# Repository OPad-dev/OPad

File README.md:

# OPad

**Low-Latency ESP32-S3 Rhythm Gaming Keypad & Telemetry Display**

A deterministic, ultra-low-latency mechanical keypad and live telemetry HUD designed for competitive osu!, osu!lazer, and rhythm games on **Linux and Windows 10/11**.

---

## ⚡ Core Principle: Latency Always Wins

> **"If a feature measurably worsens keyboard latency or latency jitter, the feature is reduced, deferred, frozen during gameplay, or removed."**

The keypad functions as a standalone 1000 Hz USB HID keyboard out of the box with zero host software running. Auxiliary features (LVGL telemetry, SQLite persistence, system tray, and tosu integration) are completely isolated from the keypress critical path.

---

## 🏗️ System Architecture

```text
                      +-------------------+
                      |    osu!lazer      |
                      +---------+---------+
                                | (observes)
                                v
                      +-------------------+
                      |       tosu        |
                      +---------+---------+
                                | (WebSocket v2)
                                v
+--------------------+   +-------------------------+
|      opad-gui      |   |       opad-daemon       |
|     (Rust/iced)    |<->|         (Rust)          |
|  - System Tray     |IPC|  - State Machine        |
|  - Layout Designer |   |  - SQLite Storage       |
|  - Configuration   |   |  - Headless Service     |
|  - Diagnostics     |   |  - tosu & Device Owner  |
+--------------------+   +------------+------------+
                                      |
                           USB CDC    |    USB HID (1000 Hz)
                                      |
                                      v
                         +-------------------------+
                         |  ESP32-S3 Touch LCD 2   |
                         |  - Eager Debounce ISR   |
                         |  - Core 0: Input & HID  |
                         |  - Core 1: LVGL & CDC   |
                         |  - ST7789 Telemetry HUD |
                         +-------------------------+
```

---

## 🔌 Hardware Target & Switch Wiring

### Supported Hardware
- **Board**: **Waveshare ESP32-S3-Touch-LCD-2** (ESP32-S3, 16MB Flash, 8MB PSRAM, 2.0" ST7789 LCD)
- **Switches**: Any two standard MX-compatible mechanical switches.

### Switch Pinout (Header P2)
Standard MX mechanical switches have no polarity. Connect each switch between its designated GPIO and ground:

| Input | Board Header & Pin | GPIO | Switch Connection |
|---|---|---|---|
| **Key 1** (Default `Z`) | **Header P2, Pin 11** | `GPIO 14` | Pin A -> Pin 11, Pin B -> GND (Pin 13) |
| **Key 2** (Default `X`) | **Header P2, Pin 12** | `GPIO 9` | Pin A -> Pin 12, Pin B -> GND (Pin 2) |
| **Ground** | **Header P2, Pin 13 / Pin 2** | `GND` | Ground Reference |

*Note: Pins 11, 12, and 13 are directly adjacent on Header P2 for simple breadboard/Dupont jumper wiring.*

These are the defaults. Each key's pin can be changed in the app under **Settings → Keys**. The list only offers header pins that work with a switch to GND:

| Header | Pins (GPIO) |
|---|---|
| **P1** | 1 (`GPIO 2`), 2 (`GPIO 4`), 3 (`GPIO 6`), 4 (`GPIO 16`), 6 (`GPIO 18`), 7 (`GPIO 21`), 8 (`GPIO 8`), 9 (`GPIO 7`), 10 (`GPIO 10`) |
| **P2** | 7 (`GPIO 15`), 8 (`GPIO 13`), 9 (`GPIO 11`), 10 (`GPIO 12`), 11 (`GPIO 14`), 12 (`GPIO 9`) |

Left out: `GPIO 19/20` (USB), `GPIO 43/44` (UART0 console), `GPIO 47/48` (touch and IMU I2C) and `GPIO 17` (pulled down on the board). Most listed pins are also wired to the camera connector, so don't use them with a camera fitted.

---

## 🛠️ Building From Source

### 1. Prerequisites (Ubuntu / Debian)
```bash
sudo apt update
sudo apt install -y build-essential pkg-config libasound2-dev libudev-dev \
    libx11-dev libxkbcommon-dev libwayland-dev libfontconfig1-dev libdbus-1-dev
```

### 2. Desktop Software Suite (Rust)
```bash
cd desktop
cargo build --release
```
The compiled binaries are produced in `desktop/target/release/`:
- `opad-daemon`: Background service.
- `opad-gui`: Graphical configuration, layout designer, and system tray.
- `opadctl`: Command-line management tool.

### 3. Firmware Build (ESP-IDF v5.5.2)
```bash
cd firmware
idf.py set-target esp32s3
idf.py build
```

---

## ⚡ Flashing the Firmware

### Option A: Via `opadctl` (Recommended)
`opadctl` drives `espflash` directly and needs no shell script and no ESP-IDF
toolchain. It asks the daemon to release the serial port first, reboots the pad
into the ROM download bootloader hands-free, writes the image and reboots back
into the app — on Linux and on Windows, with the app running:

```bash
# Update the app image only (ota_0 at 0x20000)
opadctl flash firmware/build/opad-firmware.bin

# Recovery flash: bootloader + partition table + OTA data + app
opadctl flash --full firmware/build
```

It also works with no daemon running at all, which is the state a recovery
flash usually happens in.

### Option B: Via ESP-IDF
```bash
cd firmware
idf.py -p /dev/ttyACM0 flash
```

If the pad will not enter download mode or has to be returned to stock, see
[Recovery, Reflashing & Unbinding](docs/recovery.md).

---

## 🪟 Windows Setup & Installation

**The pad needs none of this to work as a keyboard.** Plug it into any Windows
10 or 11 machine and it types immediately: HID binds to the inbox
`hidclass.sys` and the CDC port to the inbox `usbser.sys`. No `.inf`, no
WinUSB, no Zadig, no install. The software below is for configuring it, the
telemetry HUD and the lifetime counters.

1. Download `opad-setup-<version>.exe` from the GitHub Releases page and run it.
2. It installs the daemon, the GUI and `opadctl`, bundles tosu, and configures
   both to start at login. There is nothing else to do.

> **SmartScreen will warn you.** The installer is **not code-signed** yet:
> OPad is applying to SignPath Foundation for free OSS signing, which
> requires the repository to be public first. Until then, Windows shows
> "Windows protected your PC" — choose **More info → Run anyway**. Check the
> download against `SHA256SUMS` on the release page if you would rather verify
> it than trust the dialog.

Uninstall from Settings → Apps. It removes everything it installed, including
the two `Run` registry values, and asks before it touches your `opad.db` —
so a reinstall keeps your lifetime counters unless you say otherwise.

**To reset a pad completely, or hand it to someone else**, see
[Recovery, Reflashing & Unbinding](docs/recovery.md). There is no unpair button
in the app, deliberately: the only unbind is a documented reflash, and it erases
the pad's lifetime counters along with the owner record.

---

## 🚀 Linux Setup & Installation

### Option A: Pre-built Packages (Recommended)

Pre-built packages are on the GitHub Releases page. The `.deb` and `.rpm` set
up everything: the udev rule, the daemon's systemd user service, tray autostart,
the bundled `espflash`, and the ptrace capability tosu needs to read osu!'s
memory (see [docs/troubleshooting.md](docs/troubleshooting.md) §2).

Supported: every Ubuntu LTS and Debian release in support (Ubuntu 22.04, 24.04,
26.04; Debian 12, 13), RHEL / AlmaLinux / Rocky 9 and 10, current Fedora and
Arch. The release packages, bundled tosu included, need glibc 2.28 or newer.

#### Debian / Ubuntu / Pop!_OS (`.deb`):
```bash
sudo apt install ./opad_<version>_amd64.deb
# Or via dpkg:
sudo dpkg -i opad_<version>_amd64.deb
```

#### Fedora / RHEL / openSUSE (`.rpm`):
```bash
sudo dnf install ./opad-<version>.x86_64.rpm
```

#### Standalone AppImage:
```bash
chmod +x opad-x86_64.AppImage
./opad-x86_64.AppImage
```
The AppImage installs nothing system-wide. On first run it offers to install
the udev rule (it asks for your password), or run
`./opad-x86_64.AppImage install-udev` yourself. It cannot give tosu the ptrace
capability; `opadctl setup` and the Diagnostics page explain the alternative.

#### Arch Linux:
The repository's `PKGBUILD` builds from source (tosu runs on the system
`nodejs`, so see troubleshooting §2 about ptrace):
```bash
makepkg -si
```

---

### Option B: Installing From Source

#### 1. System-wide Install:
```bash
make
sudo make install
```

#### 2. User-local Install (`~/.local`):
```bash
make
make install-user
systemctl --user daemon-reload
systemctl --user enable --now opad-daemon.service
```

#### 3. Manual Udev Rules:
If not installing from package, allow non-root user access to USB CDC and ROM bootloader devices:
```bash
sudo cp packaging/linux/udev/70-opad.rules /etc/udev/rules.d/
sudo udevadm control --reload-rules && sudo udevadm trigger
```

---

## 💻 CLI Quick Reference (`opadctl`)

```bash
# Check device, daemon, and tosu state
opadctl status

# Trigger safe reconciliation
opadctl sync

# Export portable JSON backup
opadctl export backup.json

# Import validated backup
opadctl import backup.json

# Flash firmware image directly over USB
opadctl flash firmware/build/opad-firmware.bin

# Recovery flash (bootloader, partition table, OTA data and app)
opadctl flash --full firmware/build

# Reboot the pad into the ROM download bootloader and leave it there
opadctl bootloader

# Stream real-time diagnostic logs
opadctl monitor
```

---

## 📄 Documentation
- [Documentation Hub & Wiki](docs/README.md)
- [System Architecture](docs/architecture.md)
- [Project Roadmap & Hardware Variants](docs/roadmap.md)
- [OPad on Windows — as built](docs/windows-portability.md)
- [USB Framing & Protocol](docs/protocol.md)
- [Counter Reconciliation, Recovery & Unbinding](docs/recovery.md) — including the reflash / unbind path
- [Latency Testing Methodology](docs/latency-testing.md)
- [Testing & Hardware Checklist](docs/testing-checklist.md)
- [Technical Specification v1](docs/specs/technical-spec-v1.md)
- [Rapid Trigger v2 Specification](docs/specs/v2-rapid-trigger.md)

---

## 📦 Third-Party Software

OPad bundles or interacts with the following third-party software:

### tosu
- **Project**: [tosu](https://github.com/KotRikD/tosu)
- **Author**: Mikhail Babynichev and the tosu contributors
- **License**: [GNU Lesser General Public License v3.0 (LGPL-3.0)](licenses/tosu/LICENSE)
- **Redistribution Notice**: See [licenses/tosu/NOTICE](licenses/tosu/NOTICE)
- **User Replacement Rights**: Under the terms of LGPL-3.0, users are entitled to replace the bundled tosu binary with their own version. You can point the `OPAD_TOSU_PATH` (or legacy `OSUPAD_TOSU_PATH`) environment variable to a custom tosu executable, or configure an external path in the OPad desktop GUI (**Settings → tosu**).

---

## ⚖️ Trademark Disclaimer
OPad is an independent open-source hardware and software project. OPad is not affiliated with, endorsed by, or sponsored by ppy Pty Ltd or osu!. "osu!" is a registered trademark of ppy Pty Ltd.

---

## 📜 License
OPad is free and open source, software and hardware:

- **Software** — the firmware, the desktop app (daemon, GUI, CLI), the protocol, the scripts and the documentation — is licensed under the [GNU General Public License v3.0 or later](LICENSE) (`GPL-3.0-or-later`).
- **Hardware** — everything in [`hardware/`](hardware/): the PCB designs, footprints and symbols, the enclosure CAD and the production files — is licensed under the [CERN Open Hardware Licence v2, Strongly Reciprocal](hardware/LICENSE) (`CERN-OHL-S-2.0`). The scripts in `hardware/` that generate and check those files are software, under `GPL-3.0-or-later`.

You may build, modify and sell OPad. If you distribute a modified version, of the software or of the hardware, you must publish its source under the same licence. Every file's licence is recorded in [`REUSE.toml`](REUSE.toml).

Third-party components keep their own open licenses and ship with their notices:
- [tosu](licenses/tosu/LICENSE) (LGPL-3.0), built from upstream source and bundled with the desktop packages, see the section above. Not stored in this repository.
- [Montserrat](desktop/gui/assets/fonts/Montserrat-OFL.txt) fonts embedded in the GUI (SIL Open Font License 1.1).
- [nanopb](firmware/main/protocol/nanopb/LICENSE.txt) protobuf runtime vendored in the firmware (zlib license).

Libraries pulled in at build time (Rust crates, ESP-IDF components such as LVGL and TinyUSB) are not stored here and are used under their own permissive licenses.

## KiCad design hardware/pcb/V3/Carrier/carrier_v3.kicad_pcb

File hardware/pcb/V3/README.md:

# OPad V3 PCBs

| Board | Folder | Size | Status |
|---|---|---|---|
| Controller carrier V3 | `Carrier/` | 35.0 × 48.2 mm (the V1 outline plus a lug in the window for the USB cable) | Designed, routed, checked. **Not ordered, not built** |
| USB board V3 | `USB/` | 20.0 × 22.0 mm | Designed, routed, checked (2026-10-28). **Not ordered, not built** |
| MX input module V3 | `MX/` | 71.05 × 24.0 mm, 3 keys | Designed, routed, checked. **Not ordered, not built** |
| HE input module V3 | `HE/` | 71.05 × 24.0 mm, 3 keys | Designed, routed, checked. **Not ordered, not built** |

These replace every V1/V2 board (decisions H10–H18 and section 4.2 in
`docs/specs/hardware-redesign-brief.md`). **No firmware supports them yet.**
The work still to do is listed under "Before ordering" below.

## What is different from V1

- **Module cable:** a 14-way, 1.0 mm FFC replaces the JST SH 8-pin. It is reversible
  (a reversed cable only swaps signals between ESP32 pins, see Cables).
- **USB-C on its own board** at the case's rear wall (H18). It has ESD protection, a VBUS
  ferrite and capacitors, and a Schottky so a cable in the Waveshare's own port cannot
  feed this one. An 8-way FFC that reads the same from either end takes 5 V, D+ and D−
  to the carrier, which passes them to P1-14, P1-11 (GPIO20) and P1-12 (GPIO19).
  The case seats it on pins in its two M2 holes and clamps it from above; stops and the
  rear wall take the plug's push and pull, so the header sockets never do. The path is passive, so flashing and recovery work over it as over
  the Waveshare's own port.
- **The carrier's USB connector** sits on a lug in the window's USB-end rear corner,
  mouth on the USB-end edge: P1's sockets fill the rear edge, and the lug keeps clear of
  the M2 hole at the USB-end rear corner. (The V3 case does not use that hole: the USB
  board lies under it, so a support presses the rear rail instead.)
- **Three keys** on both modules, and **four corner holes** for the case's locating pins.
- **HE:**
  - The ADC is an **ADS7028** (C880341), the ADS7038's sibling. It has the same pins,
    registers, averaging and CRC, and it is in JLCPCB's assembly stock. The ADS7038 is
    only on LCSC.
  - An **LP5907 LDO** powers the sensors and the ADC reference from the cable's 5 V,
    not from the Waveshare's buck-converter 3V3.
  - CS has a pull-up, and the SPI lines have ESD protection.
- **Every part is on one side:** the top of the carrier and the USB board, the bottom of
  the modules.

## Cables

### Module (14-way FFC, 1.0 mm, any type A or B, 80 mm in the V3 case)

| Contact | 1 | 2 | 3 | 4 | 5 | 6 | 7 | 8 | 9 | 10 | 11 | 12 | 13 | 14 |
|---|---|---|---|---|---|---|---|---|---|---|---|---|---|---|
| Carrier | GND | 5V | 3V3 | GPIO8 | GPIO6 | GND | GPIO2 | GPIO4 | GND | GPIO10 | GPIO7 | 3V3 | 5V | GND |
| HE | GND | 5V | 3V3 | ID | MISO | GND | SCLK | MOSI | GND | CS | – | 3V3 | 5V | GND |
| MX | GND | – | 3V3 | ID | KEY3 | GND | – | – | GND | KEY1 | KEY2 | 3V3 | – | GND |

A reversed cable connects contact k to 15 − k. Power and ground still meet power and
ground. The module's ID arrives on GPIO7 instead of GPIO8 (both are ADC1 pins), and the
firmware swaps the other pins in the GPIO matrix. `hardware/verify/tests/test_system.py`
follows every pin both ways round. MX keeps KEY1 = GPIO10 and KEY2 = GPIO7, as on V1.

Module IDs: MX V3 = 47k/100k = 2.24 V, HE V3 = 100k/100k = 1.65 V (the class HE V2
reserved, since the ADC and pins are the same). Firmware cut-offs: 0.68 / 1.35 / 1.95 / 2.6 V.

### USB (8-way FFC, 1.0 mm, any type A or B, 80 mm in the V3 case)

| Contact | 1 | 2 | 3 | 4 | 5 | 6 | 7 | 8 |
|---|---|---|---|---|---|---|---|---|
| USB board and carrier | GND | 5V | D− | D+ | D+ | D− | 5V | GND |

The pinout reads the same from either end, so a reversed cable (k to 9 − k) meets the
same nets. D+ and D− each use two conductors, joined on both boards. The two 5V contacts
carry 1 A together (0.5 A each, connector datasheet). The connectors are a different width
from the module's, so the two cables cannot be swapped. `test_system.py` follows the jack's
D+, D− and 5 V to GPIO20, GPIO19 and P1-14 with the cable both ways round.

## Checks (MX 2026-10-23; carrier, USB, HE 2026-10-29)

| Check | Carrier | USB | MX | HE |
|---|---|---|---|---|
| KiCad ERC, DRC with zones refilled, schematic parity | 0 | 0 | 0 | 0 |
| `hardware/verify` (fab files against the intended netlist, datasheet pin drawings, JLCPCB's own part models at the CPL) | 0 errors | 0 errors | 0 errors | 0 errors |
| `hardware/verify/tests/test_system.py` (cables both ways, ID margins) | all pass | all pass | all pass | all pass |

- **Ferrite C107335 (carrier, HE):** replaces C1002 (Sunlord GZ1608D601TF), which LCSC no
  longer lists (product page not found, 2026-10-29). Same 600 Ω @ 100 MHz, 1 A instead of
  200 mA. It is an Extended part at JLCPCB, so it adds a setup fee.

- **AFA07-S08 (C262714):** JLCPCB's model draws the fitting nails 3.3 mm tall and 0.63 mm
  nearer the contacts than the maker's drawing (the same drawing as the 14-way's). Our
  pads follow the drawing. The CPL is aligned on the contacts, and the model's nails are
  allowed 0.8 mm (`MECH_TOL` in `export_v3.py`, `jlc_mech_tol` in `devices.py`).

- **CPL:** `export_v3.py` writes the CPL by fitting JLCPCB's own footprint of every part
  onto our pads. Every polarised bottom-side part therefore sits at 0° or 180°. That
  is the case the evidence covers (`hardware/verify/opadverify/jlc.py`). For that reason
  the Hall sensors are turned a quarter from V1.1; the generator asserts that their pads
  are V1.1's layout rotated, never mirrored.
- **Sensor keepout:** a 3 × 3 mm copper keepout sits round each Hall sensor, as on V1.1.

## Files

```
V3/
├── lib/                 footprints (new ones drawn from the makers' drawings) and symbols
├── Carrier/ USB/ MX/ HE/  KiCad projects, route.json (stitching vias, power track widths), production/
└── scripts/
    ├── v3lib.py         library: footprints, symbols
    ├── generate_v3.py   schematics and placed boards (overwrites the routing)
    ├── route_v3.py      Freerouting 1.9.0, retried until DRC has no error and nothing unconnected
    └── export_v3.py     V1's export_production.py checks and files, with the JLCPCB-model CPL
```

```
python3 hardware/pcb/V3/scripts/generate_v3.py [carrier] [usb] [mx] [he]
python3 hardware/pcb/V3/scripts/route_v3.py Carrier|USB|MX|HE
python3 hardware/pcb/V3/scripts/export_v3.py [Carrier] [USB] [MX] [HE]
cd hardware/verify && ../../.tools/venv/bin/python -m opadverify golden/he_v3.toml   # and carrier_v3, usb_v3, mx_v3
```

## Before ordering

1. **Case:** `hardware/3d/custom_case/V3` fits these boards in its fit check (2026-10-29),
   with the USB board in the rear-right corner. It has not been printed or test-fitted.
2. **Firmware:**
   - the ADS7028/7038 driver;
   - the third key;
   - cable-reversal detection;
   - the new ID classes;
   - the protocol and app for three keys.
3. **JLCPCB preview:** check every part sits on its pads before paying. The checker
   predicts no turning is needed (`-v` prints where pin 1 of each polarised part must be).
4. **Order 5, assemble 2** of each board first.

## Parts (JLCPCB, all in assembly stock on 2026-10-23)

| Board | Part | LCSC |
|---|---|---|
| carrier, MX, HE | JUSHUO AFA07-S14FCA-00 FFC connector | C262720 |
| carrier, USB | JUSHUO AFA07-S08FCA-00 FFC connector (in stock 2026-10-28) | C262714 |
| USB | HRO TYPE-C-31-M-12 USB-C | C165948 |
| carrier | XUNPU FH2.54-09-14PZD 1×14 socket, 8.5 mm (×2) | C7500781 |
| carrier, USB, HE | ProTek SRV05-4-P-T7 ESD array | C85364 |
| USB | Murata BLM18PG121SN1D ferrite, 2 A | C14709 |
| USB | B5817W Schottky (JLCPCB's model: pad 1 anode, pad 2 cathode) | C7420328 |
| carrier, HE | TDK MPZ1608S601ATA00 ferrite, 1 A | C107335 |
| MX | Kailh CPG151101S11 hot-swap socket (×3) | C41430893 |
| HE | TI DRV5055A3QDBZR Hall sensor (×3) | C266128 |
| HE | TI ADS7028IRTER ADC | C880341 |
| HE | TI LP5907MFX-3.3 LDO | C80670 |

The full lists, with the passives, are in each board's `production/jlcpcb/*-BOM-JLCPCB.csv`.
The cables are not assembled: any 14-way, 1.0 mm FFC, type A or B, 80 mm for the V3 case
(LCSC C54350071 type A, C54350068 type B; 100 mm, C34155 / C64627, also fits), and any
8-way, 1.0 mm FFC, type A or B, 80 mm (LCSC C54350099; the route is about 66 mm with
both ends in their connectors, and the extra bows up in the space beside the stack).

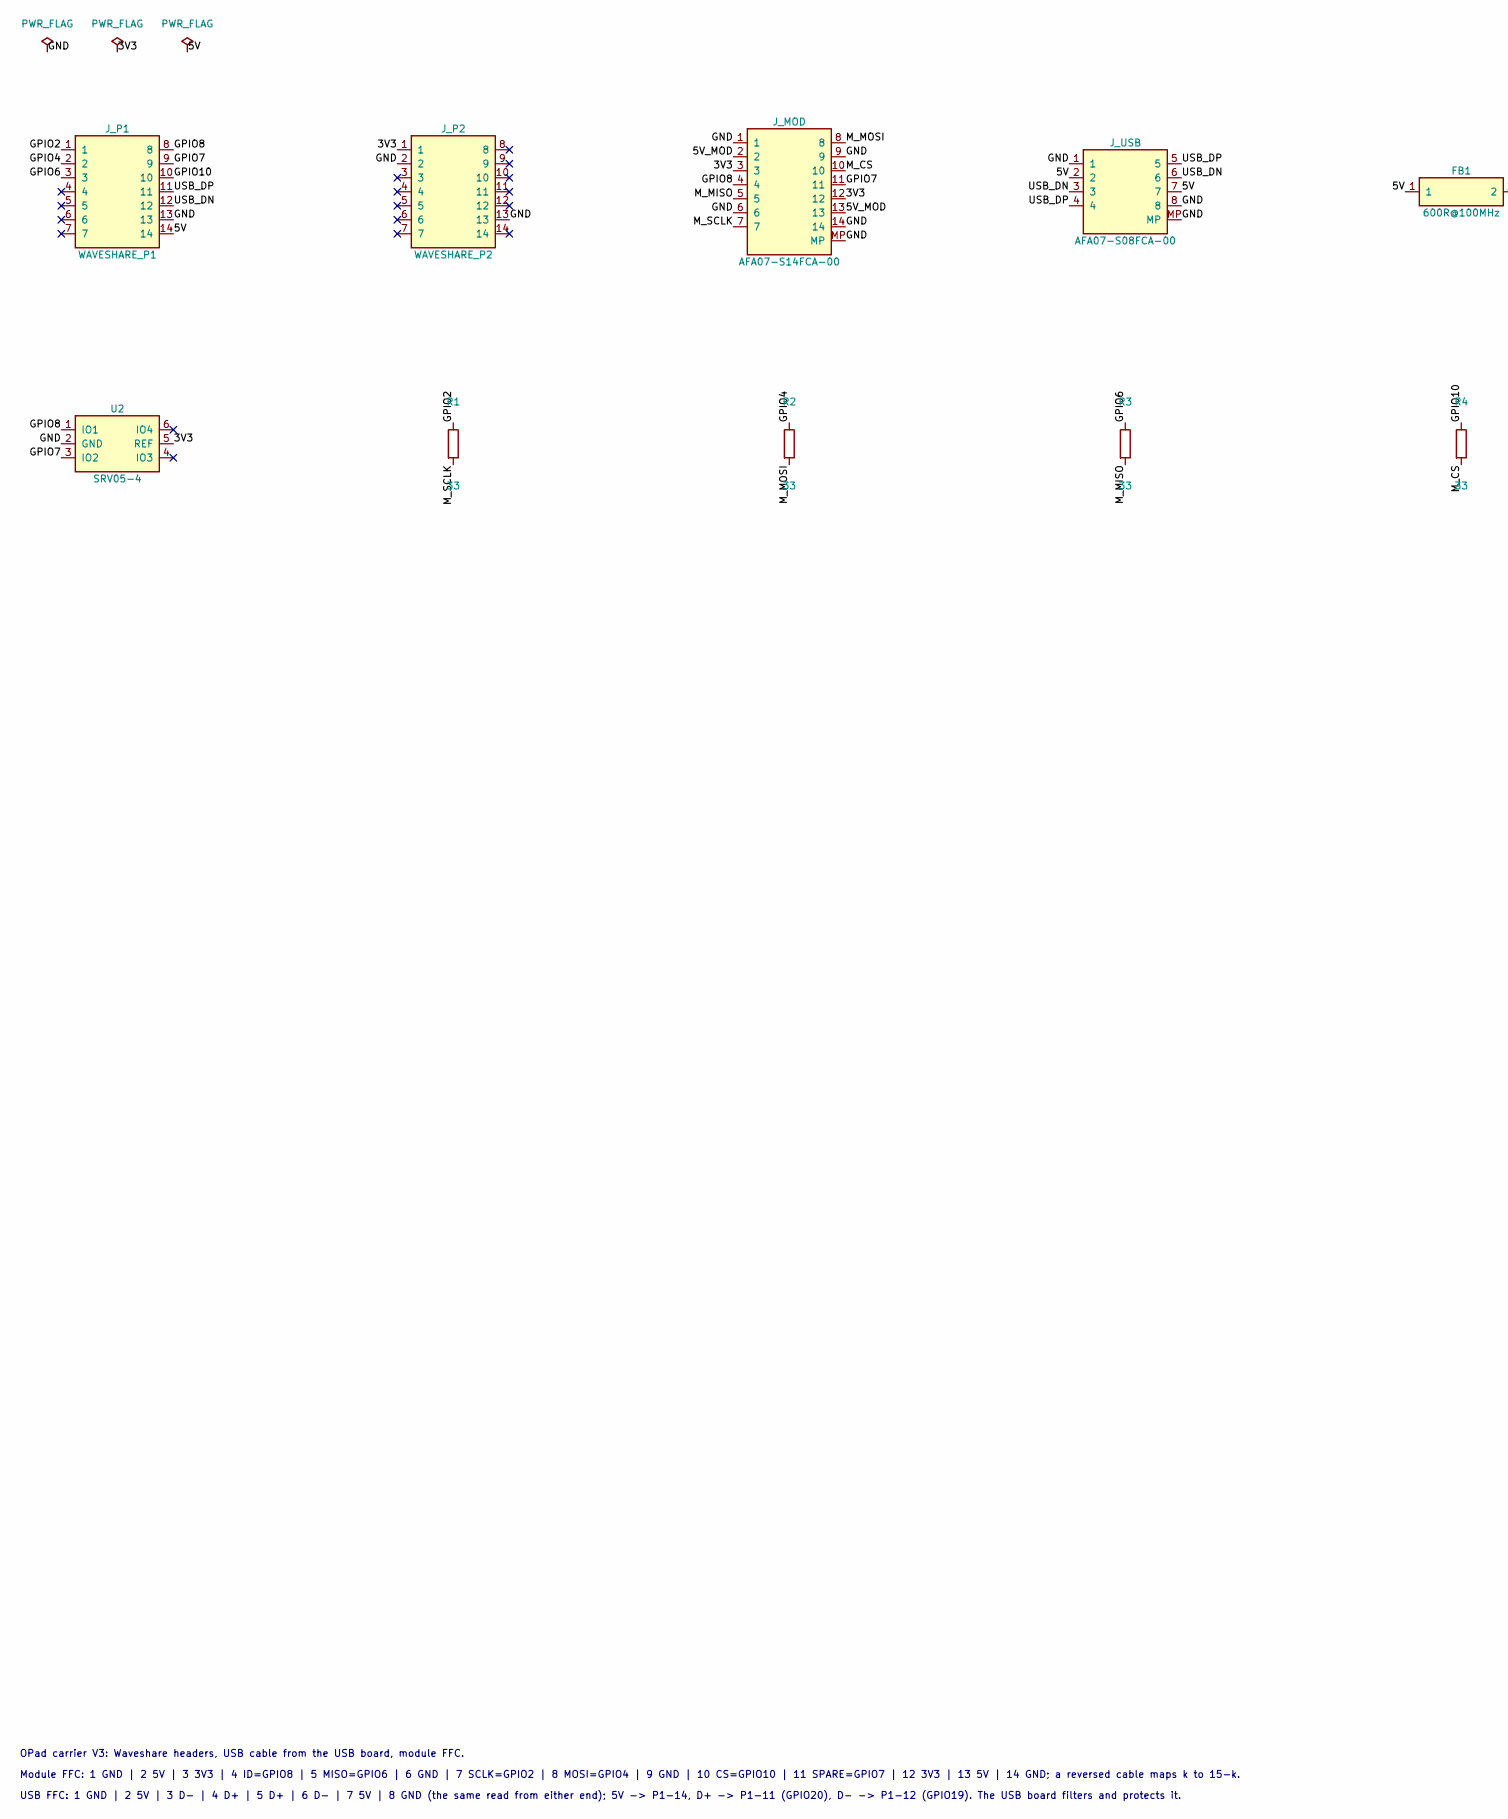
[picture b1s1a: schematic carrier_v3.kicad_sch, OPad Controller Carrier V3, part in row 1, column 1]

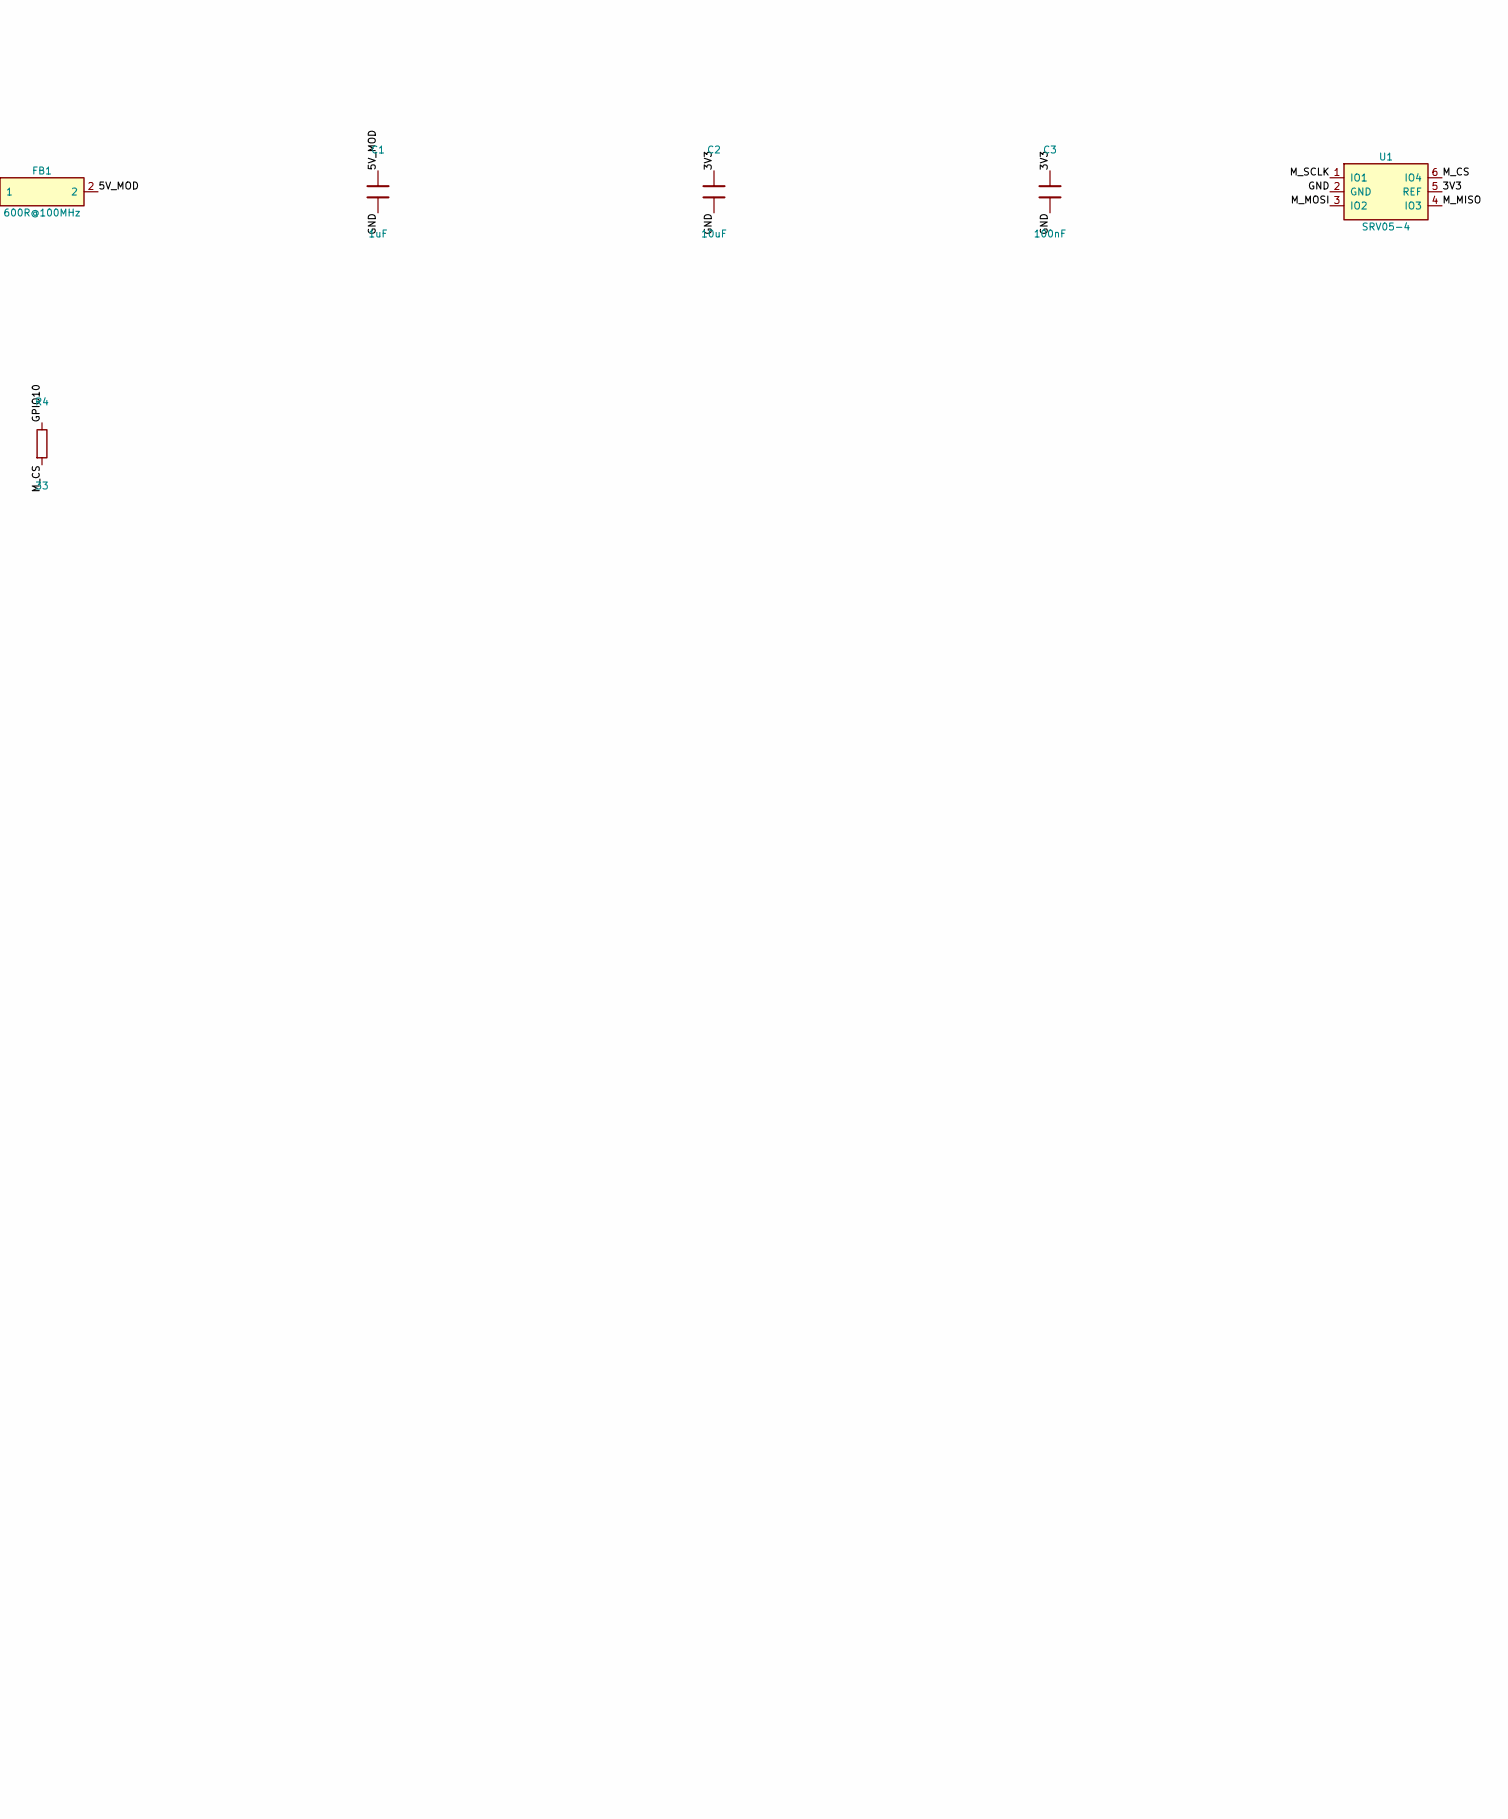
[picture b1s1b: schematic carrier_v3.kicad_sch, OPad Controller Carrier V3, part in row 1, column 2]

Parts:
C1: 1uF; C_0603_1608Metric; MPN Samsung CL10A105KB8NNNC; LCSC C15849
C2: 10uF; C_0603_1608Metric; MPN Samsung CL10A106KP8NNNC; LCSC C19702
C3: 100nF; C_0603_1608Metric; MPN YAGEO CC0603KRX7R9BB104; LCSC C14663
FB1: 600R@100MHz; L_0603_1608Metric; MPN TDK MPZ1608S601ATA00; LCSC C107335
J_MOD: AFA07-S14FCA-00; FFC_JUSHUO_AFA07-S14FCA_1x14-1MP_P1.0mm_Horizontal; MPN JUSHUO AFA07-S14FCA-00; LCSC C262720
J_P1: WAVESHARE_P1; PinSocket_1x14_P2.54mm_Vertical; MPN XUNPU FH2.54-09-14PZD; LCSC C7500781
J_P2: WAVESHARE_P2; PinSocket_1x14_P2.54mm_Vertical; MPN XUNPU FH2.54-09-14PZD; LCSC C7500781
J_USB: AFA07-S08FCA-00; FFC_JUSHUO_AFA07-S08FCA_1x08-1MP_P1.0mm_Horizontal; MPN JUSHUO AFA07-S08FCA-00; LCSC C262714
R1, R2, R3, R4: 33; R_0603_1608Metric; MPN UNI-ROYAL 0603WAF330JT5E; LCSC C23140
U1, U2: SRV05-4; SOT-23-6; MPN ProTek SRV05-4-P-T7; LCSC C85364

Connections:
/3V3: C2.1, C3.1, J_MOD.3, J_MOD.12, J_P2.1, U1.5 (REF), U2.5 (REF)
/5V: FB1.1, J_P1.14, J_USB.2, J_USB.7
/5V_MOD: C1.1, FB1.2, J_MOD.2, J_MOD.13
/GND: C1.2, C2.2, C3.2, J_MOD.1, J_MOD.6, J_MOD.9, J_MOD.14, J_MOD.MP, J_P1.13, J_P2.2, J_P2.13, J_USB.1, J_USB.8, J_USB.MP, U1.2 (GND), U2.2 (GND)
/GPIO2: J_P1.1, R1.1
/GPIO4: J_P1.2, R2.1
/GPIO6: J_P1.3, R3.1
/GPIO7: J_MOD.11, J_P1.9, U2.3 (IO2)
/GPIO8: J_MOD.4, J_P1.8, U2.1 (IO1)
/GPIO10: J_P1.10, R4.1
/M_CS: J_MOD.10, R4.2, U1.6 (IO4)
/M_MISO: J_MOD.5, R3.2, U1.4 (IO3)
/M_MOSI: J_MOD.8, R2.2, U1.3 (IO2)
/M_SCLK: J_MOD.7, R1.2, U1.1 (IO1)
/USB_DN: J_P1.12, J_USB.3, J_USB.6
/USB_DP: J_P1.11, J_USB.4, J_USB.5

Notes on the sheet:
OPad carrier V3: Waveshare headers, USB cable from the USB board, module FFC.
Module FFC: 1 GND | 2 5V | 3 3V3 | 4 ID=GPIO8 | 5 MISO=GPIO6 | 6 GND | 7 SCLK=GPIO2 | 8 MOSI=GPIO4 | 9 GND | 10 CS=GPIO10 | 11 SPARE=GPIO7 | 12 3V3 | 13 5V | 14 GND; a reversed cable maps k to 15-k.
USB FFC: 1 GND | 2 5V | 3 D- | 4 D+ | 5 D+ | 6 D- | 7 5V | 8 GND (the same read from either end); 5V -> P1-14, D+ -> P1-11 (GPIO20), D- -> P1-12 (GPIO19). The USB board filters and protects it.

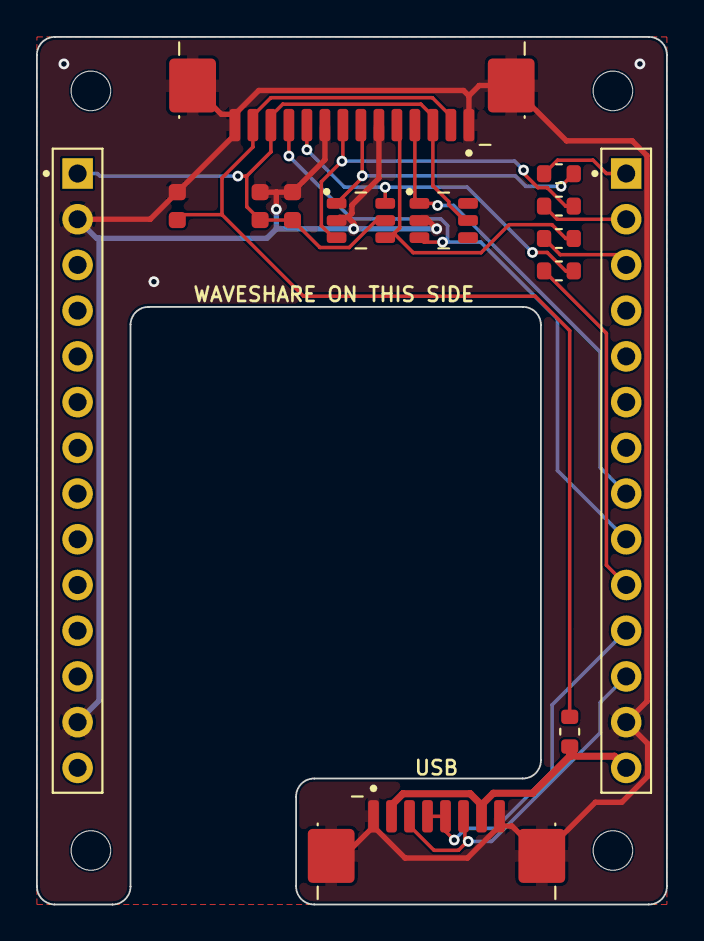
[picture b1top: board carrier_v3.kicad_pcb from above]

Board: 2 copper layers, 35.0 x 48.2 mm, 18 parts (0 on the bottom side), 16 nets.

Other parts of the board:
H1, H2, H3, H4: MountingHole_2.2mm_M2

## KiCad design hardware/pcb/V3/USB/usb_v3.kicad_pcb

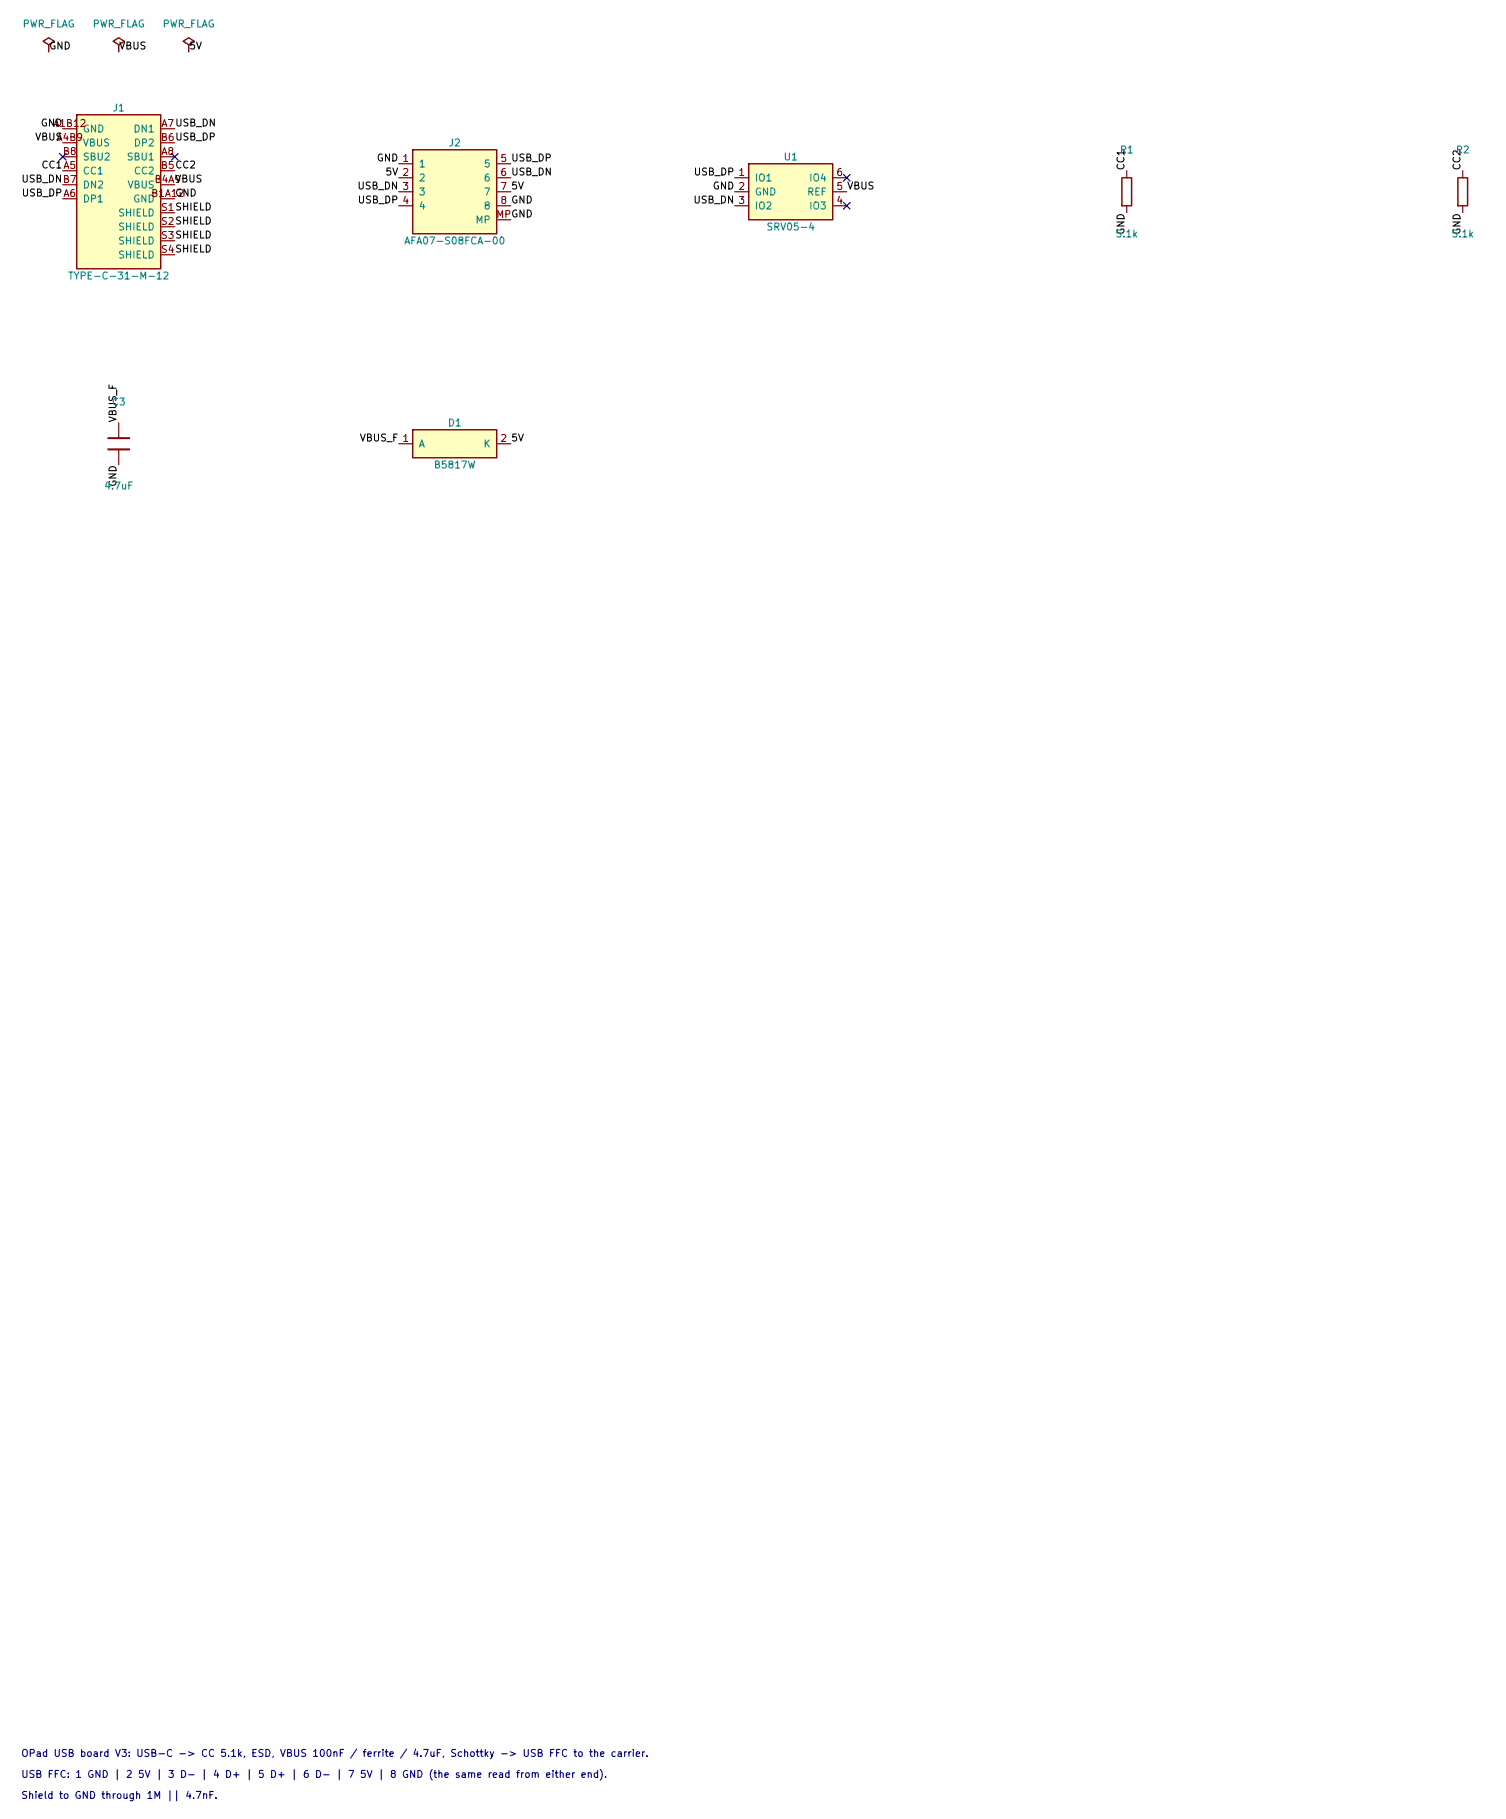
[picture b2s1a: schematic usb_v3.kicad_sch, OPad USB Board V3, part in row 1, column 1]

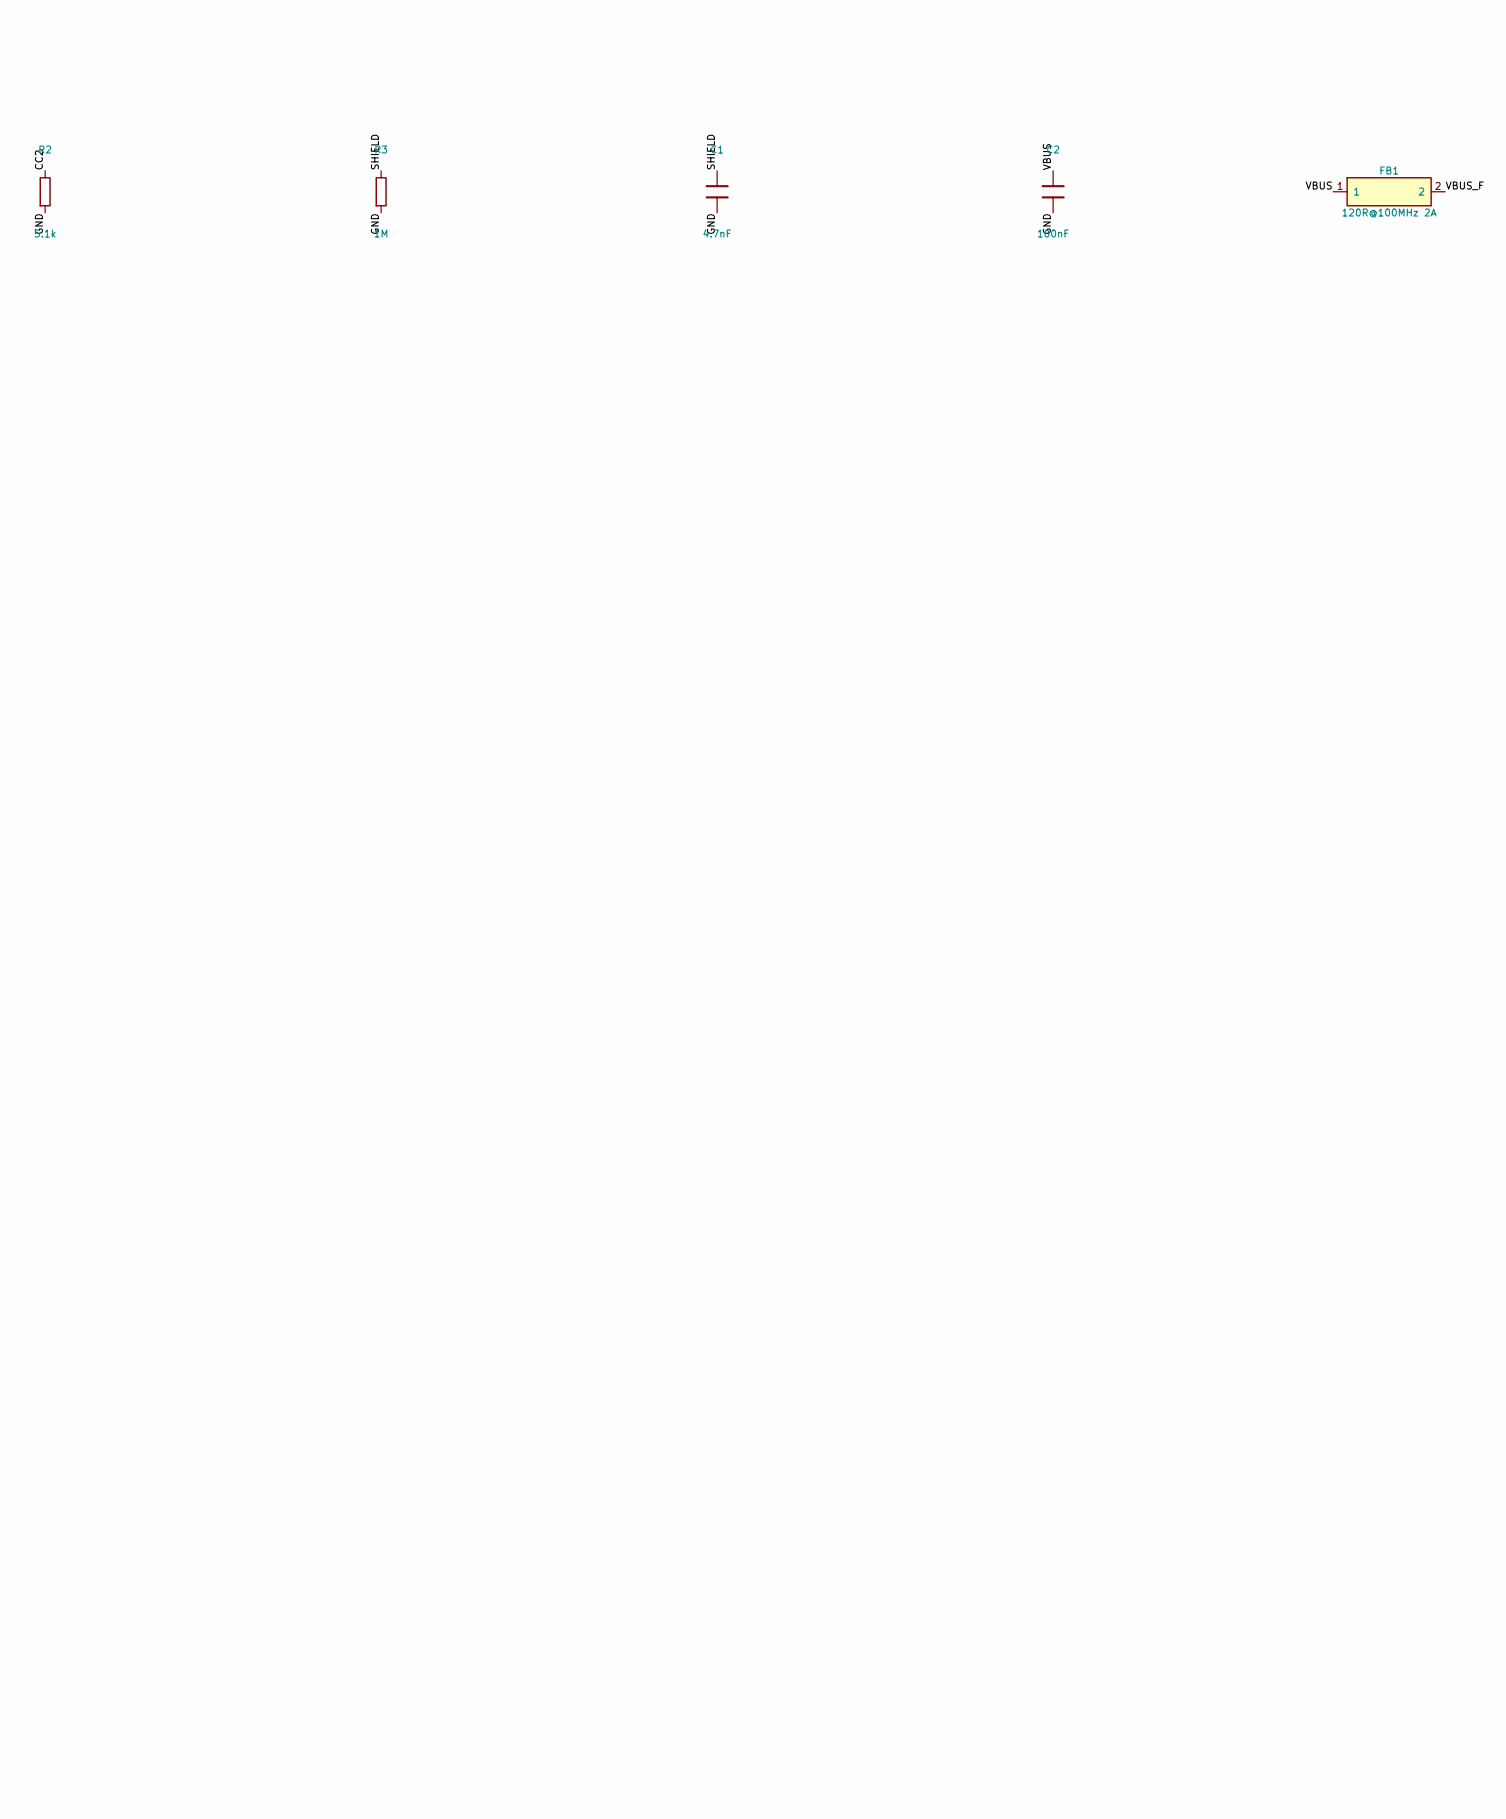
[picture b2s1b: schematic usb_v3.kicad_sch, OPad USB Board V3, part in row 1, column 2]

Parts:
C1: 4.7nF; C_0603_1608Metric; MPN FH 0603B472K500NT; LCSC C53987
C2: 100nF; C_0603_1608Metric; MPN YAGEO CC0603KRX7R9BB104; LCSC C14663
C3: 4.7uF; C_0603_1608Metric; MPN Samsung CL10A475KO8NNNC; LCSC C19666
D1: B5817W; D_SOD-123; MPN R+O B5817W; LCSC C7420328
FB1: 120R@100MHz 2A; L_0603_1608Metric; MPN Murata BLM18PG121SN1D; LCSC C14709
J1: TYPE-C-31-M-12; USB_C_Receptacle_HRO_TYPE-C-31-M-12; MPN Korean Hroparts TYPE-C-31-M-12; LCSC C165948
J2: AFA07-S08FCA-00; FFC_JUSHUO_AFA07-S08FCA_1x08-1MP_P1.0mm_Horizontal; MPN JUSHUO AFA07-S08FCA-00; LCSC C262714
R1, R2: 5.1k; R_0603_1608Metric; MPN UNI-ROYAL 0603WAF5101T5E; LCSC C23186
R3: 1M; R_0603_1608Metric; MPN UNI-ROYAL 0603WAF1004T5E; LCSC C22935
U1: SRV05-4; SOT-23-6; MPN ProTek SRV05-4-P-T7; LCSC C85364

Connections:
/5V: D1.2 (K), J2.2, J2.7
/CC1: J1.A5 (CC1), R1.1
/CC2: J1.B5 (CC2), R2.1
/GND: C1.2, C2.2, C3.2, J1.A1B12 (GND), J1.B1A12 (GND), J2.1, J2.8, J2.MP, R1.2, R2.2, R3.2, U1.2 (GND)
/SHIELD: C1.1, J1.S1 (SHIELD), J1.S2 (SHIELD), J1.S3 (SHIELD), J1.S4 (SHIELD), R3.1
/USB_DN: J1.A7 (DN1), J1.B7 (DN2), J2.3, J2.6, U1.3 (IO2)
/USB_DP: J1.A6 (DP1), J1.B6 (DP2), J2.4, J2.5, U1.1 (IO1)
/VBUS: C2.1, FB1.1, J1.A4B9 (VBUS), J1.B4A9 (VBUS), U1.5 (REF)
/VBUS_F: C3.1, D1.1 (A), FB1.2

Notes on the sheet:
OPad USB board V3: USB-C -> CC 5.1k, ESD, VBUS 100nF / ferrite / 4.7uF, Schottky -> USB FFC to the carrier.
USB FFC: 1 GND | 2 5V | 3 D- | 4 D+ | 5 D+ | 6 D- | 7 5V | 8 GND (the same read from either end).
Shield to GND through 1M || 4.7nF.

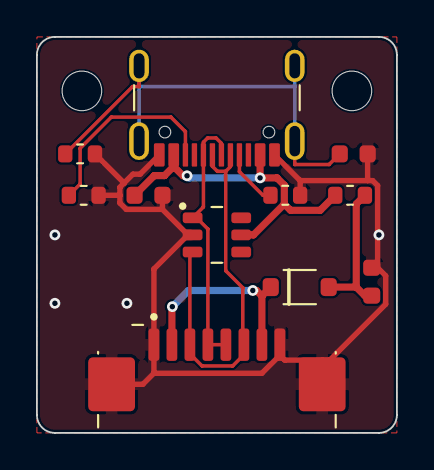
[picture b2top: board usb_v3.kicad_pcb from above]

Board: 2 copper layers, 20.0 x 22.0 mm, 13 parts (0 on the bottom side), 9 nets.

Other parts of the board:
H1, H2: MountingHole_2.2mm_M2
